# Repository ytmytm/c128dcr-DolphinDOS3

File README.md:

# DolphinDOS 3

This project [recreates work done on DolphinDOS 3 by SilverDream!](https://e4aws.silverdr.com/projects/dolphindos3/) in KiCad with some adjustments for C128DCR. Go there for a lot of information about DolphinDOS.

The goal was to get rid of 40-wire ribbon cable between daughterboard and IDC to IC adapter and plug the board directly into C128DCR mainboard into U101 (6502 CPU) footprint.

With a ribbon cable extension the same board can be still used with 1571 from C128D or standalone 1571 or installed in 1541/1541-II.

# Project

All the Kicad files are in [dolphindos3-kicad/](dolphindos3-kicad/) folder.

Also check [dolphindos3-kicad/plots/](dolphindos3-kicad/plots/) for schematic PDF and gerbers for manufacturing.

Schematic is [available there as well](dolphindos3-kicad/plots/dolphindos3-kicad.pdf).

Branch `sd-rev2a` is frozen to reflect SD! design recovered from Gerber files he published and with recreated schematic.

## Design changes

- IDC socket and CPU socket swapped around, additional footprint for pins going down to C128DCR U101 socket
- support for 64K ROM (27E512), short/open JP3 to choose which half is used; if you have C128 Kernal switcher then connect JP3 square pad there so that A15 line (pin 1 of ROM) of both C128 Kernal and 1571CR DOS changes simultaneously
- JP3 makes JP1 obsolete you can switch between stock (or JiffyDOS) and DolphinDOS on the fly; JP1 can be used to disable onboard RAM
- support for 32K (62256) and 8K (6264) SRAM chips; for 32K option additionally JP4 and JP5 choose if PIA port B bits 0 and 1 are used to select 8K bank visible in $6000-$7FFF range; this is not supported by any software right now; you can keep those jumpers open

## Parts

- 6x DIP 14 sockets
- 2x DIP 28 sockets
- 3x DIP 40 sockets
- 1x 74LS04
- 3x 74LS08
- 2x 74LS32
- 1x 62256 or 6264 SRAM
- 1x 32K or 64K EPROM/EEPROM (e.g. 27E512)
- 1x PIA 6821 (e.g. MC6821L)
- 9x 0.1uF capacitors (104)
- 4x 10K resistors
- 5x 2-pin square goldpins and jumpers
- 2x 20-pin round goldpins
- 10 wire ribbon cable (about 1m)
- 10 pin IDC socket
- 10 pin IDC connector
- user port connector

For logic chips 74xx the HCT or F series is fine too.

Optionally (not needed for C128DCR):

- 40 pin IDC socket
- 40 pin ribbon cable
- 40 pin IDC to DIP socket adapter

## C128DCR preparation

1. Desolder U101 (6502)

2. Put a socket in that place

3. Put back 6502 and test if the drive still works

## PCB assembly

Start with resistors, then solder in pins that will go down to the mainboard PCB. You need round goldpins, not square ones. After that solder in all the IC sockets. Finally add capacitors and jumpers.

I have omitted JP2 because C128DCR has drive reset built-in.

Since I have kernal switcher I should have omitted JP3 and just solder a wire between JP3 square pin and U32 pin 1 (A15 pin) from the very beginning.

For the same reason I'm not going to use JP1 to disable DolphinDOS. It's enough for me to switch between top 32K of ROM chips with DolphinDOS 3 and the bottom half with JiffyDOS. Shorting JP1 would disable PIA, RAM expansion and would use the onboard DOS ROM.

Assembly is quite easy but there is a lot of solder points - over 200. If I ever do a second revision I would replace all the logic by two GALs of just go with SMD for 74xx logic.

## Installation in C128DCR

Carefully align the pins from DD3 daughterboard with U101 socket and push it in. Put some insulation sheet over the underlying ICs just in case.

You can test the board already, even without the cable. After `UI` command it should report Dolphin DOS.

Note the cable alignment. When crimping the IDC connector make sure to align red wire with the small triangle on the connector.
I didn't put strain relief part here because that could make the whole assembly to tall and bump against drive mechanism. Having strain relief would also make it impossible to remove the table through user port opening without removing the mainboard first - it would be too tall.

## Parallel cable

I have routed the cable to the back of the computer, then under the power supply to the user port opening.

| **USER PORT** | **signal** | **Flat 10** |
| --- | --- | --- |
| B   | /FLAG2 | 1 (red) |
| C   | PB0 | 2   |
| D   | PB1 | 3   |
| E   | PB2 | 4   |
| F   | PB3 | 5   |
| H   | PB4 | 6   |
| J   | PB5 | 7   |
| K   | PB6 | 8   |
| L   | PB7 | 9   |
| 8   | /PC2 | 10  |

The user port side looks like this. Side with 9 wires with red one connected to pin B is the bottom. The last, 10th wire (`/PC`) is connected to pin 8 on the top side.

# Firmware / ROMs

Firmware is in [roms/](roms/) folder:

- [dd2_kernal_rom.bin](roms/dd2_kernal_rom.bin) - C64 DolphinDOS 2 Kernal, it works with drive's DolphinDOS 3
- [sd_dd2_kernal_rom.bin](roms/sd_dd2_kernal_rom.bin) - same, customized by SD!
- [kernal-dolphin128.bin](roms/kernal-dolphin128.bin) - C128 DolphinDOS Kernal, for C128DCR (32K U32 ROM) it has to be combined with C64 Kernal [dd2_kernal_rom.bin](roms/dd2_kernal_rom.bin) and [C64 Basic](https://www.zimmers.net/anonftp/pub/cbm/firmware/computers/c64/basic.901226-01.bin)
- [3dosa_c_27c256_payload.bin](roms/3dosa_c_27c256_payload.bin) - 1541 DolphinDOS 3 ROM
- [1571-dolphin-dos-3.bin](roms/1571-dolphin-dos-3.bin) - 1571 DolphinDOS 3 ROM, works in C128DCR (1571CR) as well as standalone 1571 or internal 1571 from C128D

## Remarks

[Supposedly](https://www.forum64.de/index.php?thread/21490-dolphindos/) the C128 Kernal ROM is based on earlier revision than the one used in C128DCR. This means it should be compared against stock ROM and reapplied on the last revision of the C128 Kernal.

The same ROM is used for all 1571 drives. The 1571CR from C128DCR has a different MFM controller, so this part supposedly doesn't work anymore. Again, if DD3 ROM would be compared against stock 1571 DOS hopefully changes could be reapplied on the 1571CR ROM. However I think it's not as important as the C128 Kernal issue.

## 1541

For 1541-II instead of DolphinDOS 3 I recommend [DolphinDOS 2 which is much simpler and uses far fewer components](https://github.com/ytmytm/1541-RAMBOardII).

Exactly the same cable pinout for 10-wire parallel cable coming in from 1541 is used in my [built-in Swiftlink coupled with CIA#2 project](https://github.com/ytmytm/c128-link232/blob/main/Swift-L%20(C128D)/plots/Link232-wifi.pdf).

# Quick tests

Use `@X` command to control DolphinDOS options. [Read the manual](docs/dolphindos.txt) (copy from [Project64](https://project64.c64.org/hw/dolphindos.txt) for all the options that you can control with `@X`.

If sucessfully enabled the directory listing should be noticeably faster (it uses RAM as a cache) and load should report start/end addresses:

# Results

Benchmark results from 64'er speed test show that in C64 mode the internal 1571 drive is almost 31 times faster on PRG LOAD than a stock 1541.

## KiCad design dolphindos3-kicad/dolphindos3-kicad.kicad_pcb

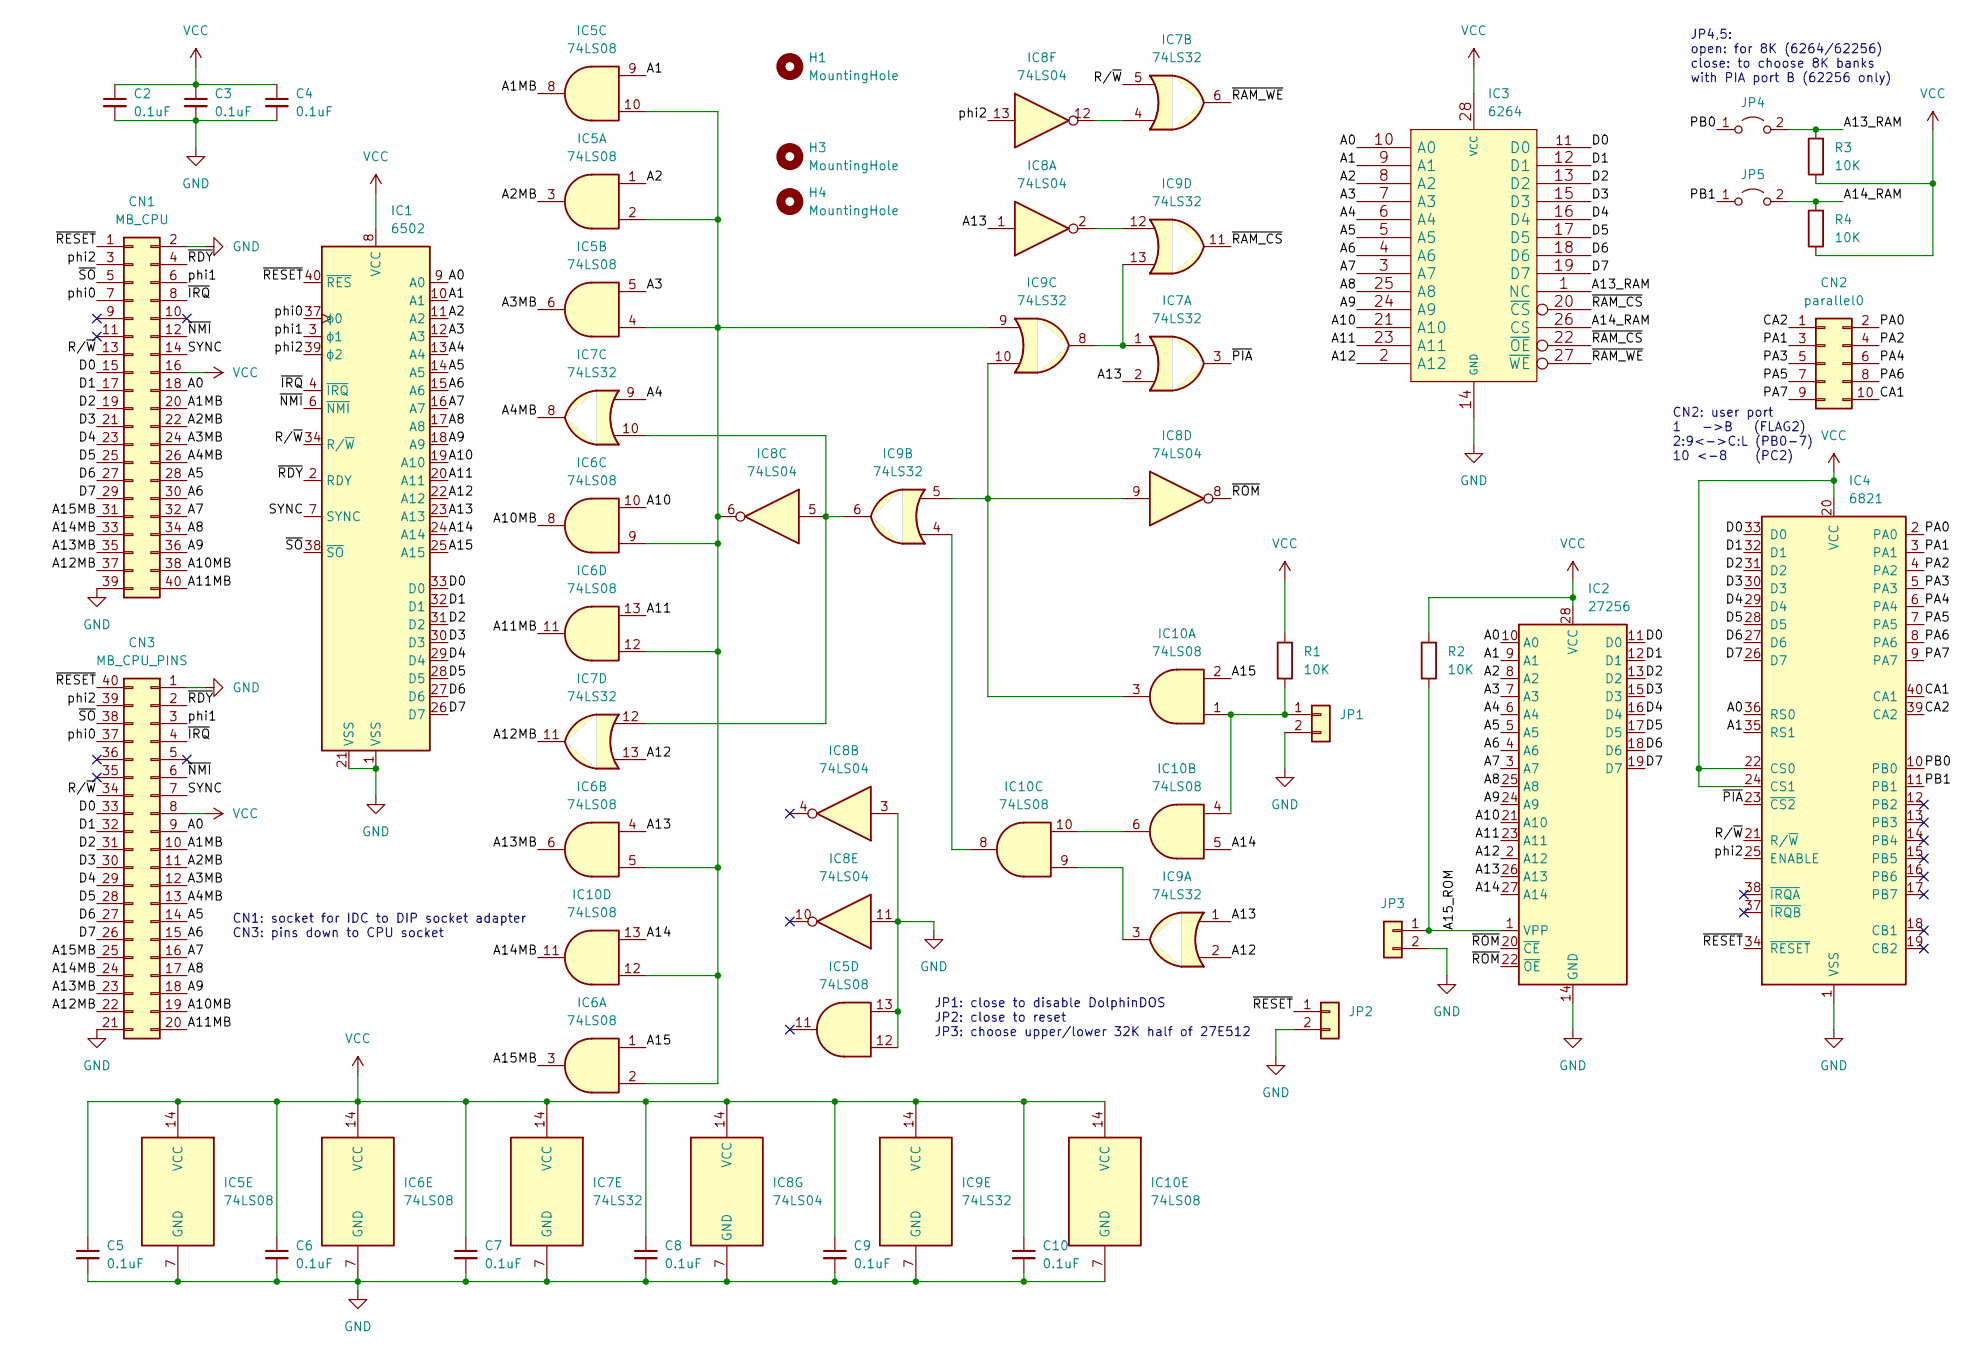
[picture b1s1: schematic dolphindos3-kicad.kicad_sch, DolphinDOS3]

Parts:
C2, C3, C4, C5, C6, C7, C8, C9, C10: 0.1uF; C_Disc_D3.4mm_W2.1mm_P2.50mm
CN1: MB_CPU; IDC-Header_2x20_P2.54mm_Vertical
CN2: parallel0; IDC-Header_2x05_P2.54mm_Vertical
CN3: MB_CPU_PINS; DIP-40_W15.24mm
H1, H3, H4: MountingHole; MountingHole_3mm
IC1: 6502; DIP-40_W15.24mm_Socket
IC2: 27256; DIP-28_W15.24mm_Socket
IC3: 6264; DIP-28_W15.24mm_Socket
IC4: 6821; DIP-40_W15.24mm_Socket
IC5, IC6, IC10: 74LS08; DIP-14_W7.62mm_Socket
IC7, IC9: 74LS32; DIP-14_W7.62mm_Socket
IC8: 74LS04; DIP-14_W7.62mm_Socket
JP1, JP2, JP3: Conn_01x02; PinHeader_1x02_P2.54mm_Vertical
JP4, JP5: Jumper_2_Open; PinHeader_1x02_P2.54mm_Vertical
R1, R2, R3, R4: 10K; R_Axial_DIN0207_L6.3mm_D2.5mm_P7.62mm_Horizontal

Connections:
/A0: CN1.18, CN3.9, IC1.9 (A0), IC2.10 (A0), IC3.10 (A0), IC4.36 (RS0)
/A1: IC1.10 (A1), IC2.9 (A1), IC3.9 (A1), IC4.35 (RS1), IC5.9
/A1MB: CN1.20, CN3.10, IC5.8
/A2: IC1.11 (A2), IC2.8 (A2), IC3.8 (A2), IC5.1
/A2MB: CN1.22, CN3.11, IC5.3
/A3: IC1.12 (A3), IC2.7 (A3), IC3.7 (A3), IC5.5
/A3MB: CN1.24, CN3.12, IC5.6
/A4: IC1.13 (A4), IC2.6 (A4), IC3.6 (A4), IC7.9
/A4MB: CN1.26, CN3.13, IC7.8
/A5: CN1.28, CN3.14, IC1.14 (A5), IC2.5 (A5), IC3.5 (A5)
/A6: CN1.30, CN3.15, IC1.15 (A6), IC2.4 (A6), IC3.4 (A6)
/A7: CN1.32, CN3.16, IC1.16 (A7), IC2.3 (A7), IC3.3 (A7)
/A8: CN1.34, CN3.17, IC1.17 (A8), IC2.25 (A8), IC3.25 (A8)
/A9: CN1.36, CN3.18, IC1.18 (A9), IC2.24 (A9), IC3.24 (A9)
/A10: IC1.19 (A10), IC2.21 (A10), IC3.21 (A10), IC6.10
/A10MB: CN1.38, CN3.19, IC6.8
/A11: IC1.20 (A11), IC2.23 (A11), IC3.23 (A11), IC6.13
/A11MB: CN1.40, CN3.20, IC6.11
/A12: IC1.22 (A12), IC2.2 (A12), IC3.2 (A12), IC7.13, IC9.2
/A12MB: CN1.37, CN3.22, IC7.11
/A13: IC1.23 (A13), IC2.26 (A13), IC6.4, IC7.2, IC8.1, IC9.1
/A13MB: CN1.35, CN3.23, IC6.6
/A13_RAM: IC3.1 (NC), JP4.2 (B), R3.2
/A14: IC1.24 (A14), IC2.27 (A14), IC10.5, IC10.13
/A14MB: CN1.33, CN3.24, IC10.11
/A14_RAM: IC3.26 (CS), JP5.2 (B), R4.2
/A15: IC1.25 (A15), IC6.1, IC10.2
/A15MB: CN1.31, CN3.25, IC6.3
/CA1: CN2.10, IC4.40 (CA1)
/CA2: CN2.1, IC4.39 (CA2)
/D0: CN1.15, CN3.33, IC1.33 (D0), IC2.11 (D0), IC3.11 (D0), IC4.33 (D0)
/D1: CN1.17, CN3.32, IC1.32 (D1), IC2.12 (D1), IC3.12 (D1), IC4.32 (D1)
/D2: CN1.19, CN3.31, IC1.31 (D2), IC2.13 (D2), IC3.13 (D2), IC4.31 (D2)
/D3: CN1.21, CN3.30, IC1.30 (D3), IC2.15 (D3), IC3.15 (D3), IC4.30 (D3)
/D4: CN1.23, CN3.29, IC1.29 (D4), IC2.16 (D4), IC3.16 (D4), IC4.29 (D4)
/D5: CN1.25, CN3.28, IC1.28 (D5), IC2.17 (D5), IC3.17 (D5), IC4.28 (D5)
/D6: CN1.27, CN3.27, IC1.27 (D6), IC2.18 (D6), IC3.18 (D6), IC4.27 (D6)
/D7: CN1.29, CN3.26, IC1.26 (D7), IC2.19 (D7), IC3.19 (D7), IC4.26 (D7)
/PA0: CN2.2, IC4.2 (PA0)
/PA1: CN2.3, IC4.3 (PA1)
/PA2: CN2.4, IC4.4 (PA2)
/PA3: CN2.5, IC4.5 (PA3)
/PA4: CN2.6, IC4.6 (PA4)
/PA5: CN2.7, IC4.7 (PA5)
/PA6: CN2.8, IC4.8 (PA6)
/PA7: CN2.9, IC4.9 (PA7)
/PB0: IC4.10 (PB0), JP4.1 (A)
/PB1: IC4.11 (PB1), JP5.1 (A)
/R/~W: CN1.13, CN3.34, IC1.34 (R/~W), IC4.21 (R/~W), IC7.5
/SYNC: CN1.14, CN3.7, IC1.7 (SYNC)
/phi0: CN1.7, CN3.37, IC1.37 (ϕ0)
/phi1: CN1.6, CN3.3, IC1.3 (ϕ1)
/phi2: CN1.3, CN3.39, IC1.39 (ϕ2), IC4.25 (ENABLE), IC8.13
/~IRQ: CN1.8, CN3.4, IC1.4 (~IRQ)
/~NMI: CN1.12, CN3.6, IC1.6 (~NMI)
/~PIA: IC4.23 (~CS2), IC7.3
/~RAM_CS: IC3.20 (~CS), IC3.22 (~OE), IC9.11
/~RAM_WE: IC3.27 (~WE), IC7.6
/~RDY: CN1.4, CN3.2, IC1.2 (RDY)
/~RESET: CN1.1, CN3.40, IC1.40 (~RES), IC4.34 (~RESET), JP2.1
/~ROM: IC2.20 (~CE), IC2.22 (~OE), IC8.8
/~SO: CN1.5, CN3.38, IC1.38 (~SO)
GND: C2.2, C3.2, C4.2, C5.2, C6.2, C7.2, C8.2, C9.2, C10.2, CN1.2, CN1.39, CN3.1, CN3.21, IC1.1 (VSS), IC1.21 (VSS), IC2.14 (GND), IC3.14 (GND), IC4.1 (VSS), IC5.7 (GND), IC5.12, IC5.13, IC6.7 (GND), IC7.7 (GND), IC8.3, IC8.7 (GND), IC8.11, IC9.7 (GND), IC10.7 (GND), JP1.2, JP2.2, JP3.2
unnamed: IC2.1 (VPP), JP3.1, R2.1
unnamed: IC7.1, IC9.8, IC9.13
unnamed: IC7.4, IC8.12
unnamed: IC7.10, IC7.12, IC8.5, IC9.6
unnamed: IC8.2, IC9.12
unnamed: IC10.1, IC10.4, JP1.1, R1.1
unnamed: IC8.9, IC9.5, IC9.10, IC10.3
unnamed: IC9.4, IC10.8
unnamed: IC9.3, IC10.9
unnamed: IC10.6, IC10.10
unnamed: IC5.2, IC5.4, IC5.10, IC6.2, IC6.5, IC6.9, IC6.12, IC8.6, IC9.9, IC10.12
VCC: C2.1, C3.1, C4.1, C5.1, C6.1, C7.1, C8.1, C9.1, C10.1, CN1.16, CN3.8, IC1.8 (VCC), IC2.28 (VCC), IC3.28 (VCC), IC4.20 (VCC), IC4.22 (CS0), IC4.24 (CS1), IC5.14 (VCC), IC6.14 (VCC), IC7.14 (VCC), IC8.14 (VCC), IC9.14 (VCC), IC10.14 (VCC), R1.2, R2.2, R3.1, R4.1

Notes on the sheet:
CN2: user port 1 ->B (FLAG2) 2:9<->C:L (PB0-7) 10 <-8 (PC2)
JP4,5: open: for 8K (6264/62256) close: to choose 8K banks with PIA port B (62256 only)
CN1: socket for IDC to DIP socket adapter CN3: pins down to CPU socket
JP1: close to disable DolphinDOS JP2: close to reset JP3: choose upper/lower 32K half of 27E512

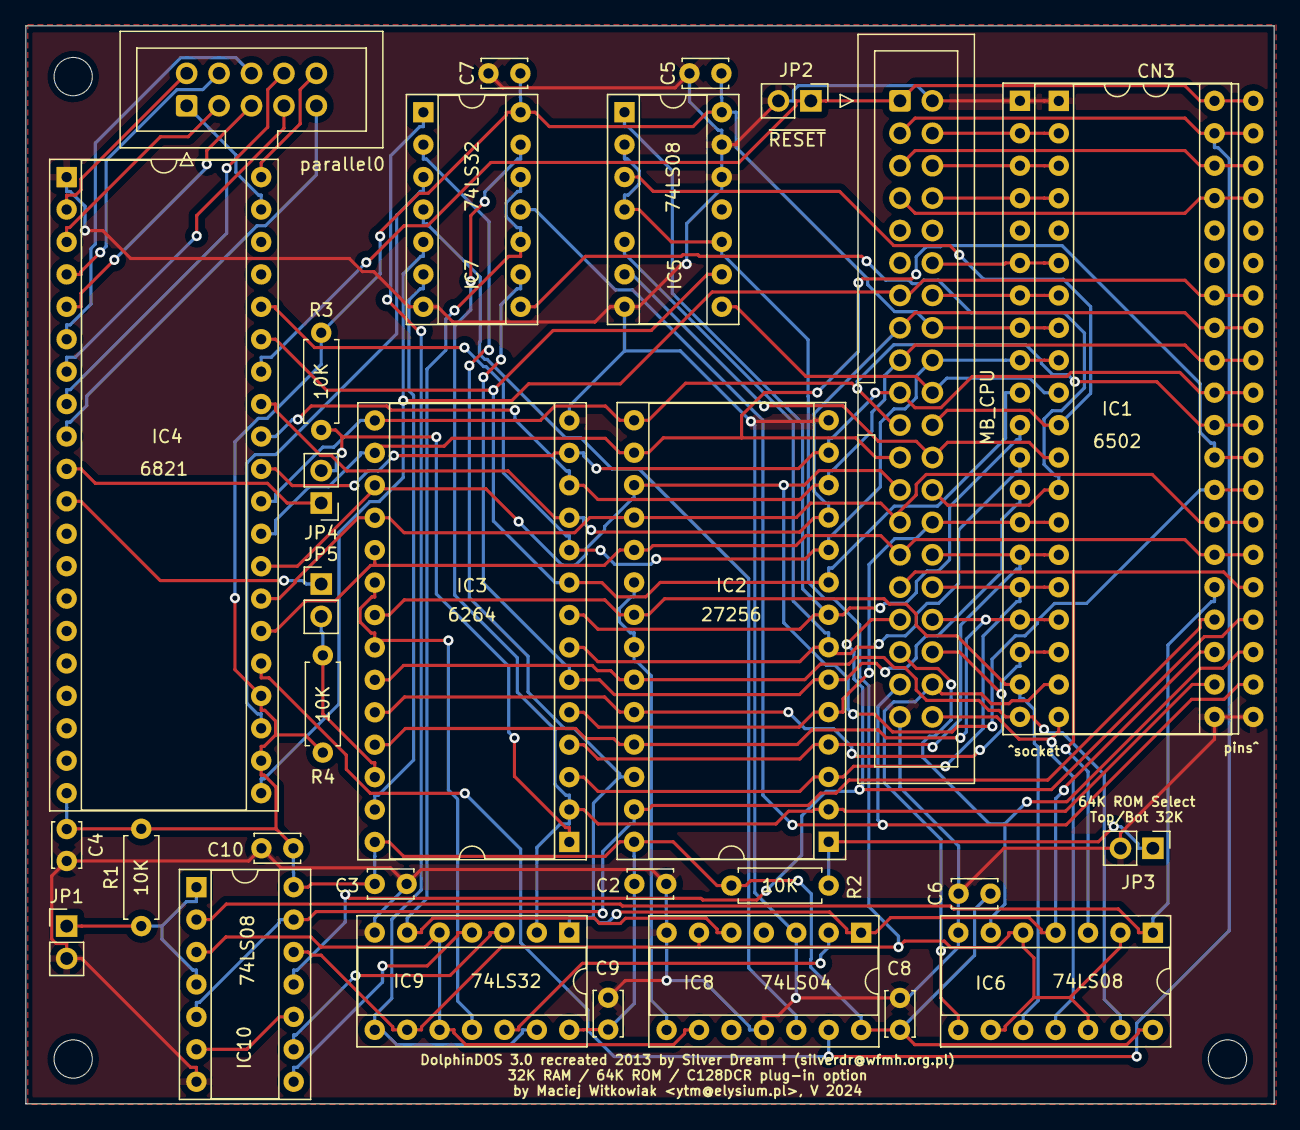
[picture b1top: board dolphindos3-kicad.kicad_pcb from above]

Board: 2 copper layers, 97.8 x 84.5 mm, 34 parts (0 on the bottom side), 75 nets.

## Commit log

2024-04-30 initial commit, redrawn schematic, not verified against SD!'s gerbers
2024-04-30 redraw without crossed lines
2024-04-30 IDC socket for parallel cable, added JP2 for drive reset to match gerbers
2024-04-30 F.Cu, B.Cu and F.Silkscreen copied from SliverDreams! rev2a gerber files, Edge.cuts eyeballed; placed parts and added footprints
2024-05-01 mods: RAM A13/14 from PIA PB, ROM A15, unused gate inputs tied to GND pcb: autorouted, parts moved for C128DCR plug-in option
2024-05-04 new gerbers as ordered today
2024-05-04 6821 datasheet
2024-05-04 ROM for 1571 (and 1571CR?)
2024-05-04 1541-II ROM
2024-05-04 C64 DolphinDOS 2/3 Kernal ROM (also for C128)
2024-05-20 C128 Kernal with DolphinDOS (for U32 in C128DCR this needs to be combined with DolphinDOS C64 Kernal)
2024-05-20 media
2024-05-20 copy of SilverDream! files
2024-05-20 C64 Kernal adjusted to SD! taste
2024-05-21 media files
2024-05-21 copy from https://project64.c64.org/hw/dolphindos.txt
